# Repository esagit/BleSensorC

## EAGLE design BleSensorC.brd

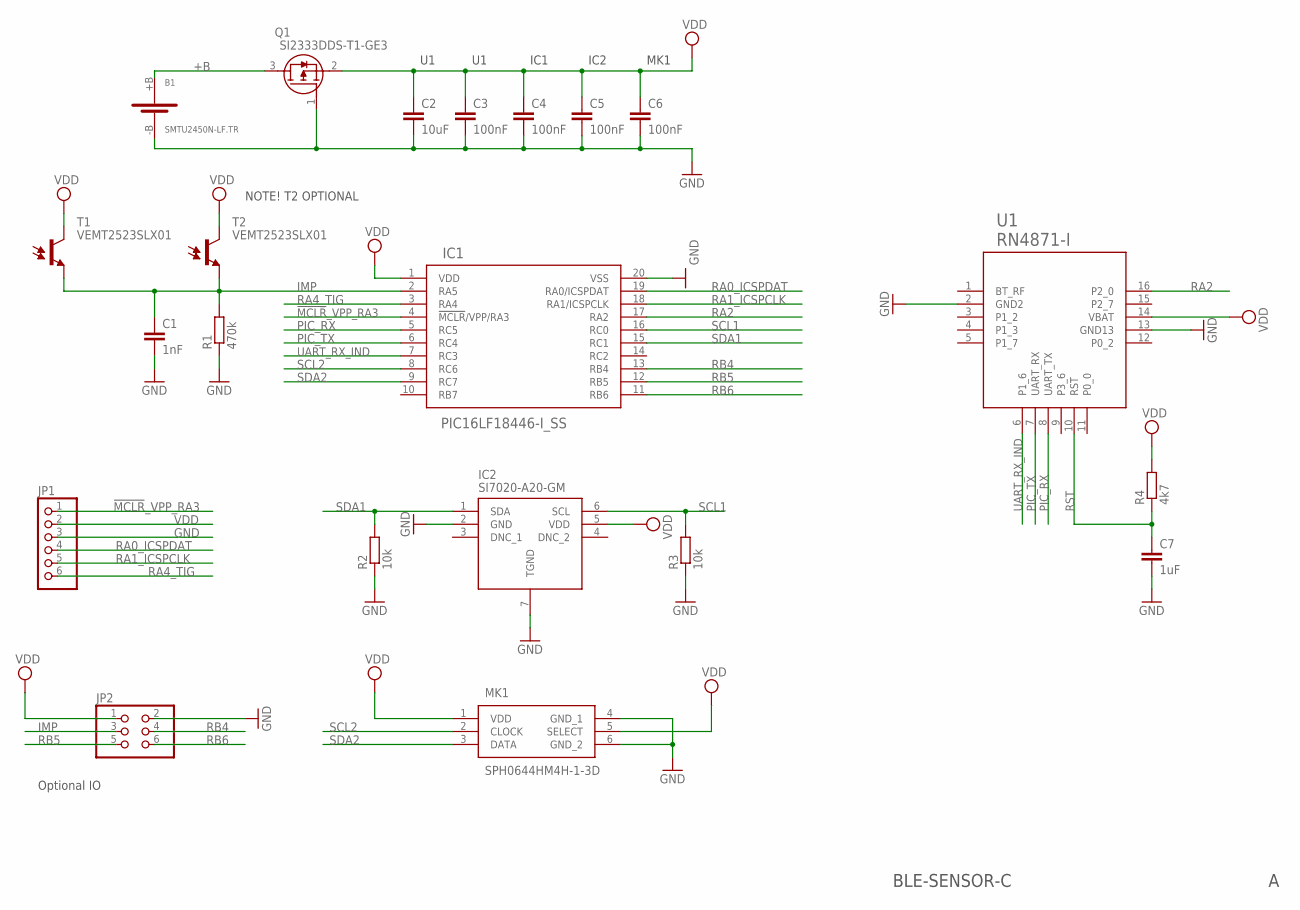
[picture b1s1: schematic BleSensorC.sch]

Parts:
B1: SMTU2450N-LF.TR; SMTU2450N-LF
C1: 1nF; C0805
C2: 10uF; C0805
C3, C4, C5, C6: 100nF; C0805
C7: 1uF; C0805
IC1: PIC16LF18446-I_SS; SOP65P780X200-20
IC2: SI7020-A20-GM; DFN-6-3X3-SI7020
JP1: PINHD-1X6-S; 1X06-S
JP2: PINHD-2X3; 2X03
MK1: SPH0644HM4H-1-3D; SOJ88P324X95-6
Q1: SI2333DDS-T1-GE3; SOT95P237X112-3
R1: 470k; R0805
R2, R3: 10k; R0805
R4: 4k7; R0805
T1, T2: VEMT2523SLX01; VEMT2523SL
U1: RN4871-I; RN4871

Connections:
!MCLR!_VPP_RA3: IC1.4 (!MCLR!/VPP/RA3), JP1.1
+B: B1.+B, Q1.3 (D)
GND: B1.-B, C1.2, C2.2, C3.2, C4.2, C5.2, C6.2, C7.2, IC1.20 (VSS), IC2.2 (GND), IC2.7 (TGND), JP1.3, JP2.2, MK1.4 (GND_1), MK1.6 (GND_2), Q1.1 (G), R1.1, R2.1, R3.1, U1.2 (GND2), U1.13 (GND13)
IMP: C1.1, IC1.2 (RA5), JP2.3, R1.2, T1.E, T2.E
PIC_RX: IC1.5 (RC5), U1.8 (UART_TX)
PIC_TX: IC1.6 (RC4), U1.7 (UART_RX)
RA0_ICSPDAT: IC1.19 (RA0/ICSPDAT), JP1.4
RA1_ICSPCLK: IC1.18 (RA1/ICSPCLK), JP1.5
RA2: IC1.17 (RA2), U1.16 (P2_0)
RA4_TIG: IC1.3 (RA4), JP1.6
RB4: IC1.13 (RB4), JP2.4
RB5: IC1.12 (RB5), JP2.5
RB6: IC1.11 (RB6), JP2.6
RST: C7.1, R4.1, U1.10 (RST)
SCL1: IC1.16 (RC0), IC2.6 (SCL), R3.2
SCL2: IC1.8 (RC6), MK1.2 (CLOCK)
SDA1: IC1.15 (RC1), IC2.1 (SDA), R2.2
SDA2: IC1.9 (RC7), MK1.3 (DATA)
UART_RX_IND: IC1.7 (RC3), U1.6 (P1_6)
VDD: C2.1, C3.1, C4.1, C5.1, C6.1, IC1.1 (VDD), IC2.5 (VDD), JP1.2, JP2.1, MK1.1 (VDD), MK1.5 (SELECT), Q1.2 (S), R4.2, T1.C, T2.C, U1.14 (VBAT)

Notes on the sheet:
IC1
IC2
MK1
Optional IO
BLE-SENSOR-C
NOTE! T2 OPTIONAL

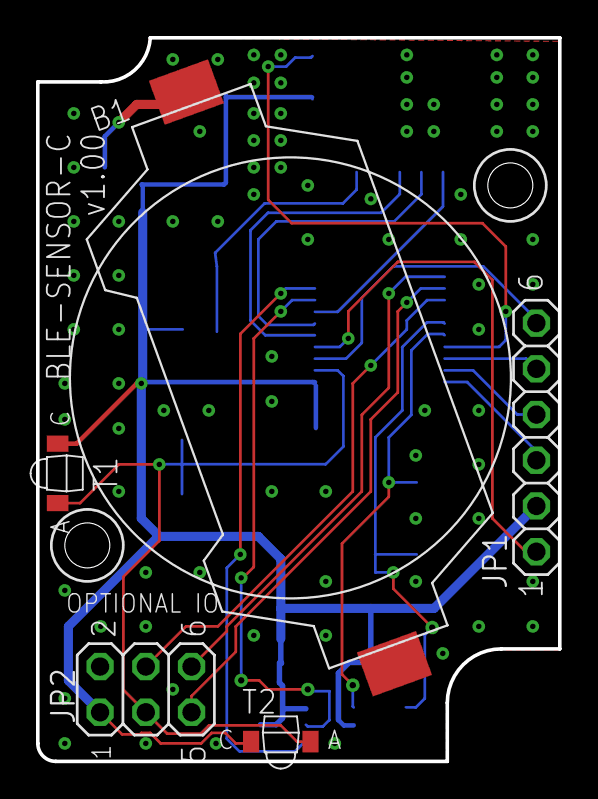
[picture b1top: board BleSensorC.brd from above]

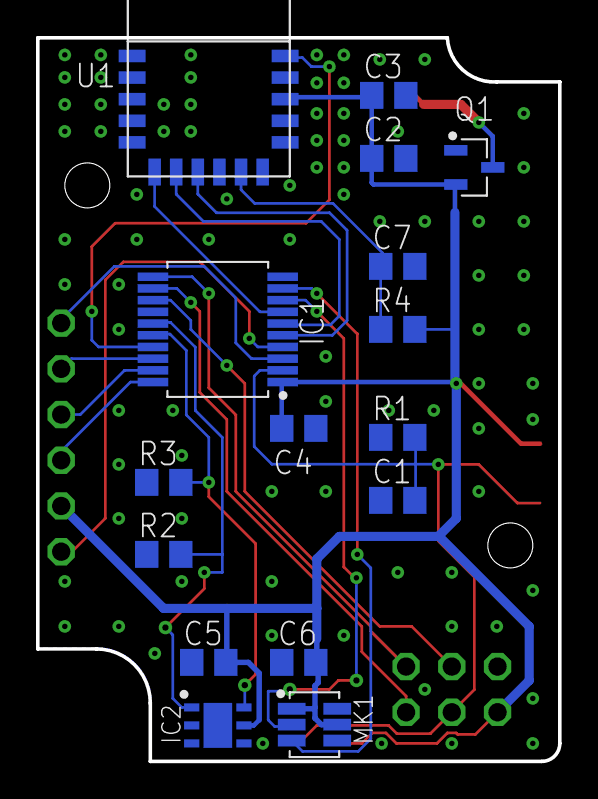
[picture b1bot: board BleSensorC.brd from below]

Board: 2 copper layers, 29.0 x 40.2 mm, 21 parts (16 on the bottom side), 20 nets.

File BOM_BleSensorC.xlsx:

Reference | Value | Footprint | Manufacture | Manufacture Part Number | Quantity | Specification
B1 | Coin Cell Battery Holders | SMD | Renata | SMTU2450N-LF.TR | 1 | https://www.mouser.fi/ProductDetail/Renata/SMTU2450N-LFTR?qs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
C1 | 1nF, 10VDC, 10%, X7R | SMD 0603 | Yageo | CC0603KRX7R6BB102 | 1 | https://www.mouser.fi/ProductDetail/Yageo/CC0603KRX7R6BB102?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
C2 | 10uF, 6.3VDC, 10%, X5R | SMD 0603 | Yageo | CC0603KRX5R5BB106 | 1 | https://www.mouser.fi/ProductDetail/Yageo/CC0603KRX5R5BB106?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
C3, C4, C5, C6 | 0.1uF, 10VDC, 10%, X7R | SMD 0603 | Yageo | CC0603KRX7R6BB104 | 4 | https://www.mouser.fi/ProductDetail/Yageo/CC0603KRX7R6BB104?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
C7 | 1uF, 10VDC, 10%, X5R | SMD 0603 | Yageo | CC0603KRX5R6BB105 | 1 | https://www.mouser.fi/ProductDetail/Yageo/CC0603KRX5R6BB105?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
R1 | 470 kOhms, 5%, 100/200 mW | SMD 0603 | Yageo | RC0603JR-07470KL | 1 | https://www.mouser.fi/ProductDetail/Yageo/RC0603JR-07470KL?q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
R2, R3 | 10 kOhms, 5%, 100/200 mW | SMD 0603 | Yageo | RC0603JR-0710KL | 2 | https://www.mouser.fi/ProductDetail/Yageo/RC0603JR-0710KL?qs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
R4 | 4,7 kOhms, 5%, 100/200 mW | SMD 0603 | Yageo | RC0603JR-074K7L | 1 | https://www.mouser.fi/ProductDetail/Yageo/RC0603JR-074K7L?qs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
IC1 | 8-bit Microcontrollers - MCU | SSOP-20 | Microchip | PIC16LF18446-I/SS | 1 | https://www.mouser.fi/ProductDetail/Microchip-Technology/PIC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
IC2 | Humidity Sensors | DFN-6 | Silicon Laboratories | SI7020-A20-GM1 | 1 | https://www.mouser.fi/ProductDetail/Silicon-Labs/SI7020-A20-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
MK1 | MEMS Microphones | SMD Rectangular | Knowles | SPH0644HM4H-1 | 1 | https://www.mouser.fi/ProductDetail/Knowles/SPH0644HM4H-1?qs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
U1 | Bluetooth BLE Module | SMD | Microchip Technology | RN4871-I/RM130 | 1 | https://www.mouser.fi/ProductDetail/Microchip-Technology/RN4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
Q1 | P-Chan MOSFET, 12 V, 6 A, 23 mOhms | SOT-23-3 | Vishay | SI2333DDS-T1-GE3 | 1 | https://www.mouser.fi/ProductDetail/Vishay-Siliconix/SI2333D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
T1 | Photodiodes 60V 215mW 35Deg PIN | SMD 2.54mm | Vishay Semiconductors | VEMD2523SLX01 | 1 | https://www.mouser.fi/ProductDetail/Vishay-Semiconductors/VE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
T2 | No assembled, optional |  |  |  | 0
JP1 | Pin header 1X6 | TH, 1X6, 2.54mm | Amphenol FCI | 68001-106HLF | 1 | https://www.mouser.fi/ProductDetail/Amphenol-FCI/68001-106HL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
JP2 | No assembled, optional |  |  |  | 0

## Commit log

2018-05-06 Initial commit
    Initial commit
2018-05-07 modified .gitattributes n .gitingnore
    modified .gitattributes n .gitingnore
2018-11-16 Fusion 3D support
    Fusion 3D support
2018-11-17 JP1 & JP2
    JP1 1X6
    JP2 2X3
2018-11-20 T1 phototransistor
    Changed T1 to Vishay VEMT2523
2018-11-22 Manual routing
    Manual routing
2018-11-23 IC1 to bottom side
    IC1 to bottom side
2018-11-23 U1 placing
    U1 placing
2018-11-27 Fixed layout, BOM & Gerber files
    Fixed layout, BOM & Gerber files
    ITEAD PCBA Enquiry
2018-11-29 Seeed order v1.00
    Footprint R0805 and C0805
